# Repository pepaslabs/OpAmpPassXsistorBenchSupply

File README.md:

# OpAmpPassXsistorBenchSupply

An adjustable voltage and current limited lab power supply, implemented with a traditional op amp and pass transistor architecture.

# Status

This design is currently broken (it oscillates).  I haven't had time to revisit it yet.

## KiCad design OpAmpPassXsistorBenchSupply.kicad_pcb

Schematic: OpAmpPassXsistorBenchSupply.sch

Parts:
C1, C3: 100uF
C2, C4, C7, C9: 1uF
C5: 10uF
C6, C8: 1000uF
C10, C11, C12, C13: 0.1uF
CON1: 2.5x5.5mm
CON2: 2.1x5.5mm
DS1: AMMETER_V
DS2: VOLTMETER
H1, H2, H3, H4: HOLE
L1: 10uH
L2: 100uH
P1, P2: CONN_1
Q1, Q2: 2N3904
Q3: TIP120; TO220
R1, R5, R6, R7, R8, R9, R10, R11, R12, R19, R20, R21, R22, R23, R24, R25, R26, R27, R28: 1
R2: 4.7k
R3, R31, R32: 47k
R4, R30: 10k
R13, R14, R15, R16, R17, R18: 1k
R29: 68k
RV1, RV4: 1k
RV2, RV3: 47k
SW1, SW2: SPDT
U1: TL431
U2: 7805
U3: LM358
U4: INA193

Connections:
GND: C1.2, C2.2, C3.2, C4.2, C5.2, C6.2, C7.2, C8.2, C9.2, C10.2, C11.2, C12.1, C13.1, CON1.2, CON1.3, CON2.2, CON2.3, DS1.2, DS1.4, DS2.3, P2.1, Q1.1 (E), Q2.1 (E), R4.2, R30.2, R32.2, RV2.1, RV3.1, SW2.2, U1.3 (A), U2.2 (GND), U3.4 (V-), U4.2 (GND)
Icontrol: RV2.2, U3.2 (-)
Isense: R31.1, U3.3 (+), U4.1 (OUT)
unnamed: R5.1, R6.1, R7.1, R8.1, SW1.1
unnamed: C3.1, C4.1, L1.2, U2.1 (IN)
unnamed: C6.1, C7.1, L2.1, R9.2, R10.2, R11.2, R12.2
unnamed: R8.2, R12.1
unnamed: R7.2, R11.1
unnamed: R6.2, R10.1
unnamed: R5.2, R9.1
unnamed: CON1.1, CON2.1, SW1.2
unnamed: R15.2, R16.1
unnamed: R13.2, R14.1
unnamed: C1.1, C2.1, L1.1, R1.2
unnamed: R17.2, U3.1
unnamed: Q1.2 (B), R17.1
unnamed: R18.2, U3.7
unnamed: Q2.2 (B), R18.1
unnamed: R3.2, RV1.3
unnamed: R4.1, RV1.1
unnamed: Q1.3 (C), Q2.3 (C), Q3.1 (B), R14.2, R16.2, SW2.3
unnamed: R31.2, RV4.3
unnamed: DS1.1, RV4.2
unnamed: R32.1, RV4.1
unnamed: RV1.2, U1.2 (R)
Shunt+: Q3.3 (E), R19.1, R20.1, R21.1, R22.1, R23.1, R24.1, R25.1, R26.1, R27.1, R28.1, U4.3 (VIN+)
Shunt-: DS2.1, P1.1, R19.2, R20.2, R21.2, R22.2, R23.2, R24.2, R25.2, R26.2, R27.2, R28.2, R29.1, U4.4 (VIN-)
VREF: R2.2, R3.1, RV2.3, RV3.3, U1.1 (K)
Vcc_filt: C8.1, C9.1, L2.2, Q3.2 (C), R1.1, R13.1, R15.1
Vcc_reg: C5.1, C10.1, C11.1, C12.2, C13.2, DS1.3, DS2.2, R2.1, U2.3 (OUT), U3.8 (V+), U4.5 (V+)
Vcontrol: RV3.2, U3.6 (-)
Vsense: R29.2, R30.1, U3.5 (+)

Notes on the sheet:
target an input range of 0V - 3V
24Vout = 3.08V
Design target: 0-24V, 0-1.5A supply
1.5A = 3.0V
Adjust for 3V
Remove 50 mOhm shunt
0.5 Ohm, 2 Watt (2 Amp limit)
0.1 Ohm, 2.5 Watt shunt (5A max)
Output Enable
Power

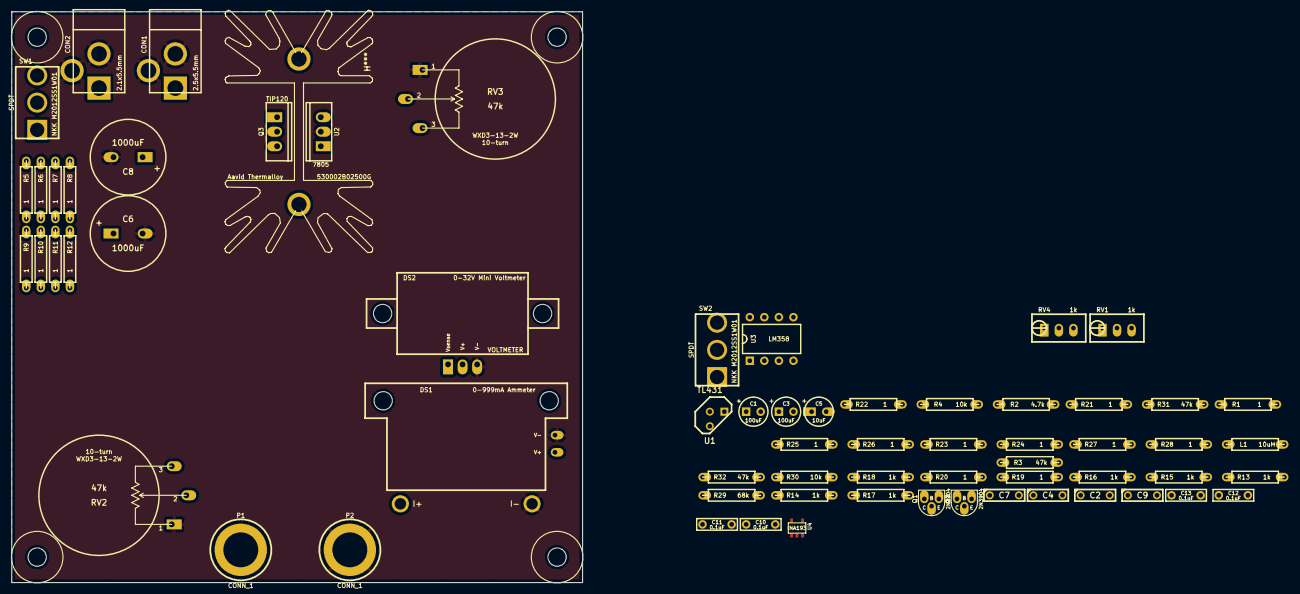
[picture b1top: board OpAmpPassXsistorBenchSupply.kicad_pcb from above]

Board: 4 copper layers, 99.7 x 99.7 mm, 70 parts (0 on the bottom side), 32 nets.

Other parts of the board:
H***: 530002B02500G

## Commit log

2014-03-29 initial project creation
2014-03-29 pulling in libraries and modules. setting up input jacks and positive and negative supply rails.
2014-03-29 implementing basic voltage control schematic
2014-03-29 adding basic current and power control stubs
2014-03-29 adding input caps
2014-03-29 adding input filter
2014-03-29 working on input filter
2014-03-29 specifying regulator passive values
2014-03-29 tweaking filter values
2014-03-29 breaking vcc out into sub sheets
2014-03-29 breaking Vee out into sub sheets
2014-03-29 breaking out additional subsheets. specifying transistor values.
2014-03-29 adding base resistor to pnp.
2014-07-04 WIP.
2014-07-04 WIP. switching to INA193. revisiting input filter.
2014-07-04 updating to latest versions of the Pepas Labs parts library.
2014-07-04 working on revamp of power supply.
2014-07-06 revision 1 being sent off to PCB house.
2014-07-06 cleaning up old files
2014-07-06 updating pdf printout.
2017-04-22 updating readme
